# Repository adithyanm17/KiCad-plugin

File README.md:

# kicad-coder

A Python library for designing, reviewing and documenting printed circuit
boards — usable directly, as an LLM tool set for any model provider, as a
Claude Code skill, or as a KiCad plugin.

**No required dependencies.** The core is standard library only, so it imports
cleanly inside KiCad's bundled Python. **KiCad is optional** — it is needed for
DRC and fabrication export, and for nothing else. Board generation, validation,
review and BOM all work on a machine with no KiCad installed.

```bash
python -m kicad_coder doctor      # what's available here
python examples/blinky.py         # build a real board, start to finish
python examples/agent_loop.py     # watch a scripted "model" drive the tools
python tests/test_kicad_coder.py  # 47 tests, no KiCad needed
```

## The core idea

Language models are good at circuits and bad at geometry. So the model never
emits geometry. It writes a typed intermediate representation — components,
nets, rules, intent — and deterministic code turns that into a board.

```
model  →  Design IR (validated)  →  placement solver  →  .kicad_pcb
                  ↑                                          ↓
                  └────────── review + DRC findings ←─────────┘
```

Every model output passes through schema validation before it touches a board.
That boundary is what separates this from a demo.

## Quick start

```python
from kicad_coder import Design, Component, BoardOutline, NetClass, FootprintLibrary
from kicad_coder import validate, review, place, write_board
from kicad_coder.fab.bom import bom_from_design, write_bom

lib = FootprintLibrary()

d = Design(name="sensor", description="I2C temperature sensor")
d.outline = BoardOutline(width_mm=30, height_mm=20)
d.rules.net_classes.append(NetClass(name="Power", track_width_mm=0.5))

d.add_component(Component("U1", "TMP102", "Package_SO:SOIC-8_3.9x4.9mm_P1.27mm",
                          mpn="TMP102AIDRLR", manufacturer="TI"))
d.add_component(Component("C1", "100n", "Capacitor_SMD:C_0603_1608Metric",
                          near=["U1"]))

d.connect("GND",  [("U1", "4"), ("C1", "2")], net_class="Power")
d.connect("+3V3", [("U1", "8"), ("C1", "1")], net_class="Power")

print(validate(d, library=lib))
for finding in review(d, lib):
    print(finding)

place(d, lib, seed=0)
write_board(d, lib, "build/sensor.kicad_pcb")
write_bom(bom_from_design(d), "build/sensor-bom.csv")
```

## Using it with a language model

The tool definitions are provider-neutral. No vendor SDK is imported anywhere
in the library.

```python
from kicad_coder.llm.tools import DesignSession
from kicad_coder.llm.adapters import to_anthropic, to_openai, to_gemini
from kicad_coder.llm.prompts import system_prompt

session = DesignSession(work_dir="build")

tools = to_anthropic(session.tools)   # Claude: Opus, Sonnet, Haiku, Fable
tools = to_openai(session.tools)      # OpenAI, DeepSeek, Kimi, Mistral, Groq,
                                      # Together, OpenRouter, vLLM, Ollama /v1
tools = to_gemini(session.tools)      # Google Gemini

result = session.call("add_components", {"components": [...]})
print(result.content)                 # feed straight back to the model
```

`session.call` never raises. A bad footprint id comes back as *"not found;
closest: Capacitor_SMD:C_0603_1608Metric"*, which models correct on the next
turn. That single property does more for reliability than any prompt wording.

`examples/agent_loop.py` has a working loop for each provider — about a dozen
lines each. Copy the branch you need.

Print the payloads without writing code:

```bash
python -m kicad_coder tools --provider gemini
python -m kicad_coder prompt --task review
```

### The 22 tools

| Group | Tools |
|---|---|
| Setup | `create_design`, `set_board_outline`, `set_design_rules`, `add_net_class` |
| Parts | `search_footprints`, `get_footprint`, `add_components`, `remove_component` |
| Wiring | `connect`, `remove_net` |
| Layout | `place_components`, `set_placement` |
| Checking | `validate_design`, `review_design`, `describe_design`, `add_note` |
| Output | `generate_board`, `generate_bom`, `run_drc`, `export_fab` |
| State | `save_design`, `load_design` |

## As a Claude Code skill

`skill/SKILL.md` is a complete skill definition. Copy the `skill` directory
into `.claude/skills/pcb-design/`, or point your skills path at it. It
activates on "design a PCB", "review my board", "generate a BOM", "run DRC".

## As a KiCad plugin

```bash
python plugin/install.py          # copy into KiCad's plugin folder
python plugin/install.py --link   # symlink instead, for development
python plugin/install.py --list   # show candidate directories
```

Then *Tools → External Plugins → Refresh*. Three entries appear:

- **Review board** — runs the design review against the open board
- **Generate BOM** — writes a consolidated CSV and Markdown BOM
- **Export design IR** — dumps the board as JSON for a model to work on

The plugin never modifies your board. It reads and reports.

## CLI

```bash
python -m kicad_coder doctor                       # environment report
python -m kicad_coder search "0603 resistor"       # find footprints
python -m kicad_coder validate design.json
python -m kicad_coder review design.json --json
python -m kicad_coder build design.json -o build/board.kicad_pcb
python -m kicad_coder bom board.kicad_pcb --format md
python -m kicad_coder drc board.kicad_pcb --json   # needs KiCad
python -m kicad_coder export board.kicad_pcb       # needs KiCad
python -m kicad_coder call add_components '{"components":[...]}'
```

## What it checks

**Validation** (blocks board generation): unknown footprints, pad numbers that
don't exist on the chosen footprint, pins shorted across two nets, duplicate
references, unknown net classes, impossible via geometry, tracks below the
process minimum, parts outside the outline.

**Review** (advisory, 14 checks): missing decoupling per IC supply pin, missing
bulk capacitance per rail, no ground net, ICs with many floating pins, power
rails left on the Default net class, board density against courtyard area,
2-layer boards that have outgrown the stackup, connectors with no ground,
missing mounting holes and test points, double-sided assembly cost,
auto-generated net names, DNP parts still wired in.

`review_design` also returns a structured facts block — supply rails, IC pin
counts, fanout, net classes. Hand that to a model and it writes an accurate
review instead of inventing one.

## Footprints

With KiCad installed, all of its `.pretty` libraries are indexed automatically.
Without it, 43 built-in parametric footprints cover the common cases: chip
passives 0402–1210 (R/C/L/LED/D), SOT-23, SOIC-8, 1×N and 2×N 2.54 mm headers,
test points and mounting holes. They are generated as standard `.kicad_mod`
S-expressions at IPC nominal density.

```python
FootprintLibrary(search_dirs=["/path/to/my-libs"])   # your own .pretty dirs
```

## File format notes

Boards are written as S-expressions directly. `version="auto"` (the default)
matches the installed KiCad so the board opens without a migration prompt;
pass `"8.0"`, `"9.0"` or `"10.0"` to pin it.

| Target | Format | `B.Cu` | Nets |
|---|---|---|---|
| KiCad 8 | `20240108` | 31 | `(net 1 "GND")` + numbered table |
| KiCad 9 | `20241229` | 2 | `(net 1 "GND")` + numbered table |
| KiCad 10 | `20260206` | 2 | `(net "GND")`, **no net table** |

Three details that are easy to get wrong, all verified against the KiCad
parser source and against boards KiCad itself wrote:

- **KiCad 9 renumbered the copper layers.** `B.Cu` is 2 in KiCad 9 and 31 in
  KiCad 8; inner layers are 4, 6, 8… versus 1, 2, 3…. The layer table must
  match the declared format version.
- **Pad and text angles are board-frame absolute**, while pad *positions* stay
  in unrotated footprint-local coordinates. A footprint rotated by R writes
  each pad at `local_angle + R`.
- **KiCad 10 dropped the numbered net table.** Nets now come into being from
  the names on pads, zones and tracks: `(net "GND")` rather than
  `(net 1 "GND")`. The parser still reads the old shape — its own comment
  calls it "legacy files (pre-10.0)".

An existing `.kicad_pro` is **merged**, not replaced: only the design rules and
net classes this library owns are overwritten, so component classes, tuning
profiles and your own settings survive a rebuild.

Design rules and net classes go in the `.kicad_pro` project file, which is
written alongside the board — KiCad 7+ reads them from there, so a board file
alone would be checked against defaults.

## Limits — stated plainly

- **No routing, no autorouter.** Boards come out with footprints, nets and a
  ground pour. Route in KiCad, or export Specctra DSN to Freerouting. Expect
  unconnected-item DRC violations until you do; that is not a defect.
- **No schematic.** The IR *is* the netlist. No ERC, no symbol libraries.
- **No simulation.** Signal integrity, thermal behaviour and impedance are out
  of scope.
- **Pin numbers, not pin functions.** The library knows a SOIC-8 has pads 1–8.
  It does not know pad 4 is ground on your specific part. Checking pin
  assignments against the datasheet remains a human job.
- **Zones are emitted unfilled.** Filling needs `pcbnew`; press `B` in KiCad,
  or fill via a plugin.

## Verified against KiCad 10.0.6

Both example boards were generated and then checked with the real
`kicad-cli pcb drc`. Result: **zero errors and zero warnings**, apart from the
expected `unconnected_items` — one per pin-pair that still needs routing
(9 for `blinky`, 13 for the agent-loop board). Gerbers, both drill files, the
job file and the pick-and-place CSV all export and zip correctly.

Getting there caught four real bugs that only a live KiCad could expose, all
now fixed and covered by tests:

| Bug | Symptom |
|---|---|
| `fp_circle` courtyard read as a bounding box | `end` is a point *on* the circle, so mounting holes got a zero-height box and parts were placed on top of them |
| Courtyard assumed centred on the footprint origin | A 2-pin header's courtyard sits 1.28 mm off centre → `courtyards_overlap` |
| Overlap check compared origins, not courtyard centres | False-positive overlaps on off-centre footprints |
| Library `attr` flags overwritten | Adding `smd` to a TestPoint made the board copy differ from the library → `lib_footprint_mismatch` |

Two more were caught by the 15,450-footprint library itself: search ranked
`R_0201_0603Metric` above `R_0603_1608Metric` for "0603 resistor" (an 0201
imperial part *is* 0603 metric — a model would have picked a part a third of
the intended size), and placement ignored the ~1.2 mm that reference
designators extend past the courtyard, clipping silkscreen at the board edge.

Boards are written in KiCad 9 format by default, which KiCad 10 opens and
migrates cleanly. Pass `version="8.0"` for wider backward compatibility.

## Layout

```
kicad_coder/
  ir/            typed IR + validation      types.py, validate.py
  library/       footprint discovery        footprints.py, builtin.py
  place/         placement solver           engine.py
  backends/      file emitters              sexpr.py, layers.py, board.py,
                                            pcbnew_backend.py
  fab/           KiCad toolchain            toolchain.py, drc.py, exports.py,
                                            bom.py
  review/        design review              rules.py
  llm/           tools + adapters           tools.py, adapters.py, prompts.py
  cli.py
skill/SKILL.md   Claude Code skill
plugin/          KiCad action plugin + installer
examples/        blinky.py, agent_loop.py
tests/           47 tests, no KiCad required
```

## Roadmap

The natural next steps, roughly in order of value:

1. **Specctra DSN export** → Freerouting round trip, closing the routing gap.
2. **Parts API integration** (Nexar/Octopart, DigiKey) to validate MPNs and
   pull stock, price and lifecycle into the BOM.
3. **KiCad 9 IPC API backend** (`kipy`) alongside the S-expression writer — it
   is pip-installable and version-stable, unlike the SWIG bindings.
4. **Circuit blocks**: reusable parameterised sub-circuits (LDO, USB-C sink,
   crystal, level shifter) so a model composes known-good designs.
5. **Schematic emission** (`.kicad_sch`) so the netlist round-trips into
   Eeschema and `kicad-cli sch erc` becomes available.

## Licence

MIT.

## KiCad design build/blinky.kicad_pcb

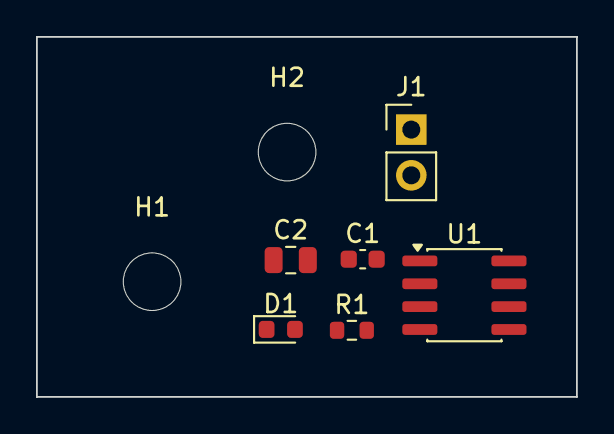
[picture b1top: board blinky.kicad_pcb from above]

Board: 2 copper layers, 30.0 x 20.0 mm, 8 parts (0 on the bottom side), 4 nets, no tracks yet.

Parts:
C1: 100n; C_0603_1608Metric
C2: 10u; C_0805_2012Metric
D1: LED_RED; LED_0603_1608Metric
H1, H2: M3; MountingHole_3.2mm_M3
J1: PWR_IN; PinHeader_1x02_P2.54mm_Vertical
R1: 330; R_0603_1608Metric
U1: ATtiny85; SOIC-8_3.9x4.9mm_P1.27mm

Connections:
+5V: C1.1, C2.1, J1.1, U1.8
GND: C1.2, C2.2, D1.2, J1.2, U1.4
LED_A: R1.1, U1.5
LED_K: D1.1, R1.2

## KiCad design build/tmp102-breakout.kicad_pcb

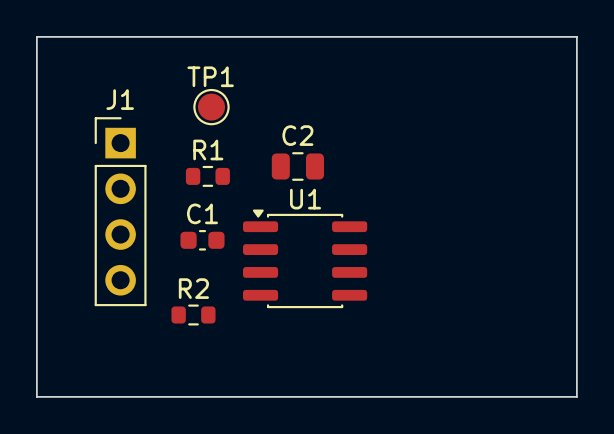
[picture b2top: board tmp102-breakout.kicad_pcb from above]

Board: 2 copper layers, 30.0 x 20.0 mm, 7 parts (0 on the bottom side), 4 nets, no tracks yet.

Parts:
C1: 100n; C_0603_1608Metric
C2: 10u; C_0805_2012Metric
J1: I2C; PinHeader_1x04_P2.54mm_Vertical
R1, R2: 4k7; R_0603_1608Metric
TP1: 3V3; TestPoint_Pad_D1.5mm
U1: TMP102; SOIC-8_3.9x4.9mm_P1.27mm

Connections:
+3V3: C1.1, C2.1, J1.1, R1.1, R2.1, TP1.1, U1.8
GND: C1.2, C2.2, J1.2, U1.4
SCL: J1.4, R2.2, U1.2
SDA: J1.3, R1.2, U1.1
